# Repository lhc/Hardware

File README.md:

# Desenvolvimento de HW LHC
Desde a sua fundação vários projetos de HW Hardware abertos foram desenvolvidos no LHC, usando diferentes processadores e ferramentas. Este repositório contém todos os projetos já desenvolvidos no LHC.

# Contribua e participe dos projetos com Hardware no LHC
Acesse o nosso forms e se conecte ao time do Laboratório Hacker de Campinas, através da criação de sua conta no forum e conversando com o pessoal sobre os diversos projetos. [https://discourse.lhc.net.br](https://discourse.lhc.net.br/c/hardware/21)

# Projetos
 2024
- [LHCbit](https://github.com/lhc/Hardware/tree/main/LHCbit)
- 
- [Venda limitada, pegue a sua placa antes que acabe](https://forms.gle/h3qhtFoRbykofKP68)
- [Construindo sua placa em KICAD](https://github.com/lhc/Hardware/tree/main/Oficinas/monte-sua-placa-kicad)
- [nodeLHC](https://github.com/lhc/Hardware/tree/main/nodeLHC)
- [nodeLHC-ESP32](https://github.com/lhc/Hardware/tree/main/nodeLHC-ESP32)

# Oficinas
- [Evento: Construindo sua placa em KiCad](https://github.com/lhc/Hardware/tree/main/Oficinas/monte-sua-placa-kicad)

# Portes
- [Porte da LHCbit para NuttX](https://github.com/apache/nuttx/blob/master/Documentation/platforms/xtensa/esp32s3/boards/esp32s3-lhcbit/index.rst)

# Bibliotecas
- [KiCad LHC](https://github.com/lhc/Hardware/tree/main/Libraries/lhc_kicad_library)

# Contribuidores
- Leandro Pereira
- Douglas Esteves
- Jorge Guzman
- Manassés Souza
- Marcelo Junqueira
- Matheus Brito
- Estevan
- Pedro Minatel
- Rafael Estevam
- Alexandre Fernandes
- Rodrigo Azevedo
- Gustavo Ortenzi

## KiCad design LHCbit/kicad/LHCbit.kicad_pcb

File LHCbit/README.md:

# LHCBbit

# O que é esse repositório ou projeto?
LHCbit  é uma placa de desenvolvimento para a comunidade, uma ferramenta de aprendizado open-source, composta por:
- ESP32-S3 - Microcontrolador com wifi e bluetooth
- STM32WLE5 - Microcontrolador ARM cortex M4 com LoRa
- Display LCD color 0.96
- LED RGB
- 2 botões
- Conector USB type C
- Padrão Microbit, sendo possível usar todos os projetos open source voltadas para a microbit.

- 

Esse repositório fica com os principais arquivos do hardware LHCbit, lista BOM (bill of material)  e logs da evolução do projeto como texto sobre via readme.md, com chamadas, links, pré-vendas e atualização das etapas da execução do projeto aberto.

Como todo repositório de projeto é algo vivo e com constantes atualizações e melhorias no projeto, então fique convidado a colaborar.

# Como funciona?
É um projeto aberto e colaborativo, funciona de forma bem simples, basta entrar em contato com os participantes e comparecer nas atividades anunciadas pelo Laboratório Hacker de Campinas, esse projeto envolve pessoas que realizaram o desenvolvimento em seu tempo livre e conforme sua disponibilidade. Para mais detalhes procurar as pessoas envolvidas que um projeto inclusive e estão disponíveis para explicar e coletar feedback.

O Projeto tem sua licença descrita, basta contribuir, replicar, comentar, é interessante notificar e passar feedback do que foi feito ou melhorias para o projeto manter sua evolução de aprimoramento, também citar e manter a licença que foi dada ao projeto.

# Quem usará esse repositório ou projeto?
Hackers, desenvolvedores de hardware, professores com interesse em construções de placas PCB, Pesquisadores universitários e técnicos e entusiastas que usarão esse repositório, não temos muitas restrições. Podendo utilizar esse projeto e algumas referências de projetos anteriores para aprender, replicar, desenvolver em cima evoluindo a ideia e projeto, citar em projeto ou usar aprendizagem envolvida para construções de novos projetos. Basta manter a ética e respeitar as licenças de projetos abertos.

# Qual o objetivo deste projeto?
O objetivo deste projeto é a construção de um hardware aberto e colaborativo para que pessoas consigam desenvolver seus projetos pessoais, ou conjuntos de pessoas passe pelas etapas de desenvolvimento de hardware até uma implementação de aplicação com o hardware desenvolvido. Ganhando experiência no que tem de tecnologia disponível para hardware e suas aplicações.

Teremos novas etapas desse projeto que é execuções de atividades e projetos com esse hardware. Para isso acompanhe a nossa lista de discussão sobre:

# Como faço para que esse projeto funcione na minha máquina?
Para que você consiga ter uma boa experiência em baixar os arquivos na sua máquina, conseguindo replicar, modificar ou desenvolver. Basta baixar os arquivos em seu equipamento local, utilizar as ferramentas adequadas para edição e construções do projeto.

Os esquemáticos foram escritos com a ferramenta [Altium](https://www.altium.com/), mas contribuições para portar para outras ferramentas serão bem vindas.
A princípio pode ser utilizado [essa ferramenta web](https://www.altium.com/viewer/) para visualizar os esquemáticos.

As evoluções do firmware (getting started) poderão ser acompanhadas [nesse projeto](https://github.com/lhc/LHCbit/tree/main)

# Como posso ajudar neste projeto?
Você também pode contribuir de diversas formas, seja revisando a documentação, arquivos CAD do hardware.
Gerando um PR Pull Request de melhorias conforme suas experiências e testes sobre hardware.
Divulgar e marcar o projeto nas redes sociais ou citar os nossos links como referência, ou até mesmo escrevendo e participando dos nossos encontros.

# Qual a licença para este projeto ?
Esse projeto está sobre a licença:
[Revisando arquivo de licença]

# Fotos do projeto

# Checklist Review 0.1
- O VCC e GND estava em curto, revisado por Leandro Pereira

# Checklist Review 0.2

| Itens           | Check | Double Check  |
|---------------------|----------|----------|
| Alimentação 3V3| OK |  |
| LoRa RAK3172-SiP|  |  |
| Reset e Boot| OK |  |
| USB Type C | OK |  |
| OLED|  |  |
| ESP32-S3-16R8 pinout| OK |  |

- [x] [Bill of Materials BOM](Templates/BOM%20Default%20Template.xlsx)

Oficina de apresentação do projeto
[definindo] eventos.lhc.net.br

# Equipe
 - Leandro Pereira
 - Douglas Esteves
 - Manasses
 - Matheus Brito
 - Marcelo Junqueira
 - Estevan

# Agradecimentos especial aos apoiadores do Projeto
- Daniel Barbosa
- L.
- Juliana Karoline
- Fabio Barros
- Luciano Ramalho
- Jomar Silva
- Estevan Castilho

# LOG
- 24/07/2024 Status do projeto (e-mail aos apoiadores)
- 18/07/2024 Reunião interna para apresentar LHCbit aos associados e definiação da fabricação da pcb para o display
- 12/07/2024 Update e consulta aos apoiadores do projeto (e-maisl aos apoiadores)
- 20/06/2024 Reunião interna para comunicar apoiadores e documentar projeto
- 13/06/2024 Status do projeto (e-mail aos apoiadores)
- 25/04/2024 update README
- 15/08/2024 Montagem final da LHCbit edition collectibles
- 05/09/2024 Apresentação sobre o projeto no LHC e remoto
- 12/09/2024 [Porte da LHCbit para NuttX](https://github.com/apache/nuttx/blob/master/Documentation/platforms/xtensa/esp32s3/boards/esp32s3-lhcbit/index.rst)
- 26/09/2024 Reunião e avaliação do github
- 03/10/2024 Reunião e revisão de hardware e github

# Contatos:
 - [Discourse](https://discourse.lhc.net.br/c/hardware/21)

# Contribuidores

<table>
<tr>
    <td align="center" style="word-wrap: break-word; width: 127.5; height: 127.5">
        <a href=https://github.com/EstevesDouglas>
            
            <br />
            <sub style="font-size:14px"><b>Douglas Esteves</b></sub>
        </a>
    </td>
    <td align="center" style="word-wrap: break-word; width: 127.5; height: 127.5">
        <a href=https://github.com/LeandroTE>
            
            <br />
            <sub style="font-size:14px"><b>Leandro Pereira</b></sub>
        </a>
    </td>
    <td align="center" style="word-wrap: break-word; width: 127.5; height: 127.5">
        <a href=https://github.com/manasouza>
            
            <br />
            <sub style="font-size:14px"><b>Manassés Loiola de Souza</b></sub>
        </a>
    </td>
</tr>
</table>

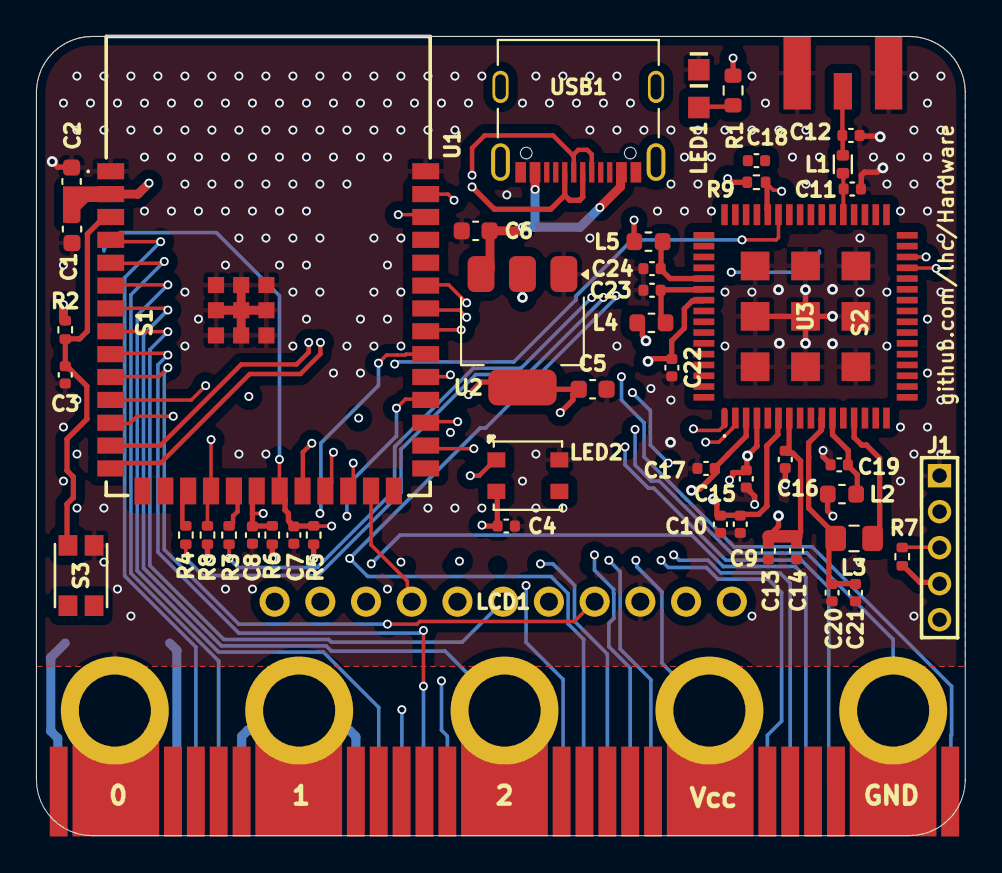
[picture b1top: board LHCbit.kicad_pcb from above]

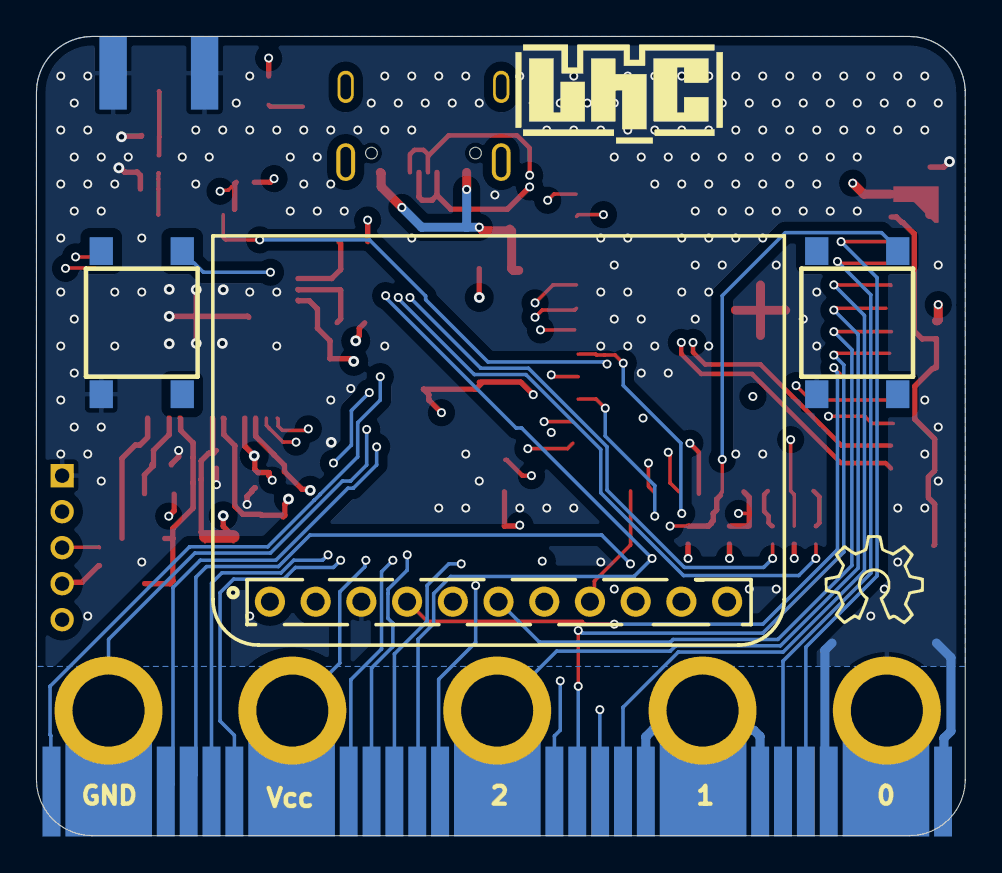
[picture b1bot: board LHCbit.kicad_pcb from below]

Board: 4 copper layers, 51.6 x 44.4 mm, 51 parts (4 on the bottom side), 46 nets.

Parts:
C1, C2, C5, C6: C-EUC0603; C_0603_1608Metric
C3, C4, C7, C8, C9, C10, C11, C12, C13, C14, C15, C16, C17, C18, C19, C20, C21, C22, C23, C24: C-EUC0402; C_0402_1005Metric
J1: 62000511121
JX1: SMACONNECTOR_EDGE_UFL; SMA_EDGELAUNCH_UFL
L1: Ferrite bead 0402; L0402 - rounded
L2, L4, L5: Ferrite bead 0603; L_0603_1608Metric
L3: L_0805_2012Metric_Pad1.15x1.40mm_HandSolder
LCD1: Adafruit 0.96" TFT LCD; ADafruit_0.96_Display
LED1: CHIPLED_0805
LED2: SK6812MINI_NOPoly; SK6812MINI
MB1: MICRO:BIT_EDGE; MICROBIT_EDGE
R1: R-US_R0603; R_0603_1608Metric
R2, R3, R4, R5, R6, R7, R8, R9: R-US_R0402; R_0402_1005Metric
S1, S2: DTSM-6; Tactile_6.6x6x4.3_DTSM-6
S3: 434153017835; 434153017835_3.2x2.9x1.7
U1: ESP32-S3-WROOM-1; ESP32S3WROOM1N16R2
U2: NCP1117LP; SOT-223
U3: RAK3172-SiP; RAK3172SiP
USB1: USB-Type-C-12402012E212A; AMPHENOL_12402012E212A

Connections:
+3V3: C1.1, C2.1, C4.2, C5.1, C9.1, C10.1, C13.1, C14.1, C15.1, C16.1, C17.1, C22.1, J1.4, L2.1, L4.1, L5.1, LCD1.1 (VIN), LED2.4 (VDD), MB1.Vcc (+3.3V), R1.2, R2.2, R5.2, R6.2, R7.2, R8.2, R9.2, U1.2 (3V3), U2.2 (VO), U2.4 (VO), U3.3 (VDD_1), U3.4 (VBAT), U3.6 (VREF+), U3.7 (VDDA), U3.55 (VDD_2)
/BOOT_STM32: R8.1, U1.18 (IO10), U3.43 (BOOT0)
/CS: MB1.P16 (#16/P0.16), U1.6 (IO6)
/D+: U1.14 (IO20), USB1.A6 (D+_A), USB1.B6 (D+_B)
/D-: U1.13 (IO19), USB1.A7 (D-_A), USB1.B7 (D-_B)
/EN: C3.1, R2.1, S3.3, U1.3 (EN)
/ESP_UART1_RX: R3.1, U1.19 (IO11)
/ESP_UART1_TX: R4.1, U1.17 (IO9)
/LED_RGB: LED2.3 (DI), U1.22 (IO14)
/LORA_RX: R4.2, U3.30 (PA3/UART2_RX)
/LORA_TX: R3.2, U3.29 (PA2/UART2_TX)
/MISO: LCD1.5 (MISO), MB1.P14 (#14/MISO/P0.22), U1.9 (IO16)
/MOSI: LCD1.6 (MOSI), MB1.P15 (#15/MOSI/P0.21), U1.8 (IO15)
/NRST: J1.5, R9.1, U1.11 (IO18), U3.44 (NRST)
/P0: MB1.P0 (PAD1/AIN2/P0.01), U1.38 (IO2)
/P1: MB1.P1 (PAD2/AIN3/P0.02), U1.31 (IO38)
/P2: MB1.P2 (PAD3/AIN4/P0.03), U1.7 (IO7)
/P3: MB1.P3 (#3/LEDCOL1/AIN5/P0.04), U1.39 (IO1)
/P4: MB1.P4 (#4/LEDCOL2/AIN6/P0.05), U1.35 (IO42)
/P6: MB1.P6 (#6/LEDCOL9/P0.12), U1.34 (IO41)
/P7: MB1.P7 (#7/LEDCOL8/P0.11), U1.33 (IO40)
/P8: MB1.P8 (#8/P0.18), U1.29 (IO36)
/P9: MB1.P9 (#9/LEDCOL7/P0.10), U1.28 (IO35)
/P10: MB1.P10 (#10/LEDCOL3/AIN7/P0.06), U1.24 (IO47)
/P12: MB1.P12 (#12/P0.20), U1.12 (IO8)
/RF_Output: C11.2, L1.1, U3.37 (RF_OUT)
/SCK: LCD1.4 (SCK), MB1.P13 (#13/SCK/P0.23), U1.10 (IO17)
/SCL: MB1.P19 (#19/SCL/P0.00), U1.5 (IO5)
/SDA: MB1.P20 (#20/SDA/P0.30), U1.4 (IO4)
/SDCS: LCD1.10 (SDCS), U1.32 (IO39)
/SW1: C7.1, MB1.P5 (#5/BUTTON_A/P0.17), R5.1, S1.4, U1.21 (IO13)
/SW2: C8.1, MB1.P11 (#11/BUTTON_B/AIN0/P0.26), R6.1, S2.4, U1.20 (IO12)
/TFTCS: LCD1.7 (TFTCS), U1.23 (IO21)
/TFTRESET: LCD1.8 (RESET), U1.25 (IO48)
/TFT_DC: LCD1.9 (TFTDC), U1.30 (IO37)
/T_SWCLK: J1.2, U3.2 (PA14)
/T_SWDIO: J1.3, R7.1, U3.1 (PA13)
GND: C1.2, C2.2, C3.2, C4.1, C5.2, C6.2, C7.2, C8.2, C9.2, C10.2, C11.1, C12.1, C13.2, C14.2, C15.2, C16.2, C17.2, C19.2, C20.2, C21.2, C22.2, C23.2, C24.2, J1.1, JX1.GND@1 (GND1), JX1.GND@2 (GND2), JX1.GND@3 (GND3), JX1.GND@4 (GND4), LCD1.3 (GND), LED1.C, LED2.2 (VSS), MB1.GND, S1.1, S2.1, S3.4, U1.1 (GND_1), U1.40 (GND_2), U1.41 (GND_3), U1.42 (GND_4), U1.43 (GND_5), U1.44 (GND_6), U1.45 (GND_7), U1.46 (GND_8), U1.47 (GND_9), U1.48 (GND_10), U1.49 (GND_11), U2.1 (GND), U3.12 (GND_1), U3.28 (GND_2), U3.35 (GND_3), U3.36 (GND_4), U3.38 (GND_5), U3.39 (GND_6), U3.46 (GND_7), U3.47 (GND_8), U3.52 (GND_9), U3.56 (GND_10), U3.65 (GND_11), U3.66 (GND_12), U3.67 (GND_13), U3.68 (GND_14), U3.69 (GND_15), U3.70 (GND_16), U3.71 (GND_17), U3.72 (GND_18), U3.73 (GND_19), USB1.A1_B12 (GND), USB1.B1_A12 (GND)
unnamed: C12.2, JX1.P (ANT), L1.2
unnamed: LED1.A, R1.1
unnamed: C19.1, L2.2, U3.11 (VDDMPS)
unnamed: C24.1, L5.2, U3.53 (VDDPA)
unnamed: C23.1, L4.2, U3.54 (VDDRF)
unnamed: C20.1, C21.1, L3.1, U3.10 (VFBSMPS)
unnamed: L3.2, U3.13 (VLXSMPS)
Vbus: C6.1, U2.3 (V+), USB1.A4_B9 (VBUS), USB1.B4_A9 (VBUS)

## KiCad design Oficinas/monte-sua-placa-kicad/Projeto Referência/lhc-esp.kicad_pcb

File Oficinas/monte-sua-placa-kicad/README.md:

# Evento: Construindo sua placa em KICAD

Repositório do evento "Construindo sua placa em KICAD"

Página do Evento: https://eventos.lhc.net.br/event/live-construindo-sua-placa-em-kicad

Link da Live: https://www.youtube.com/watch?v=B9zf6GB_SSQ

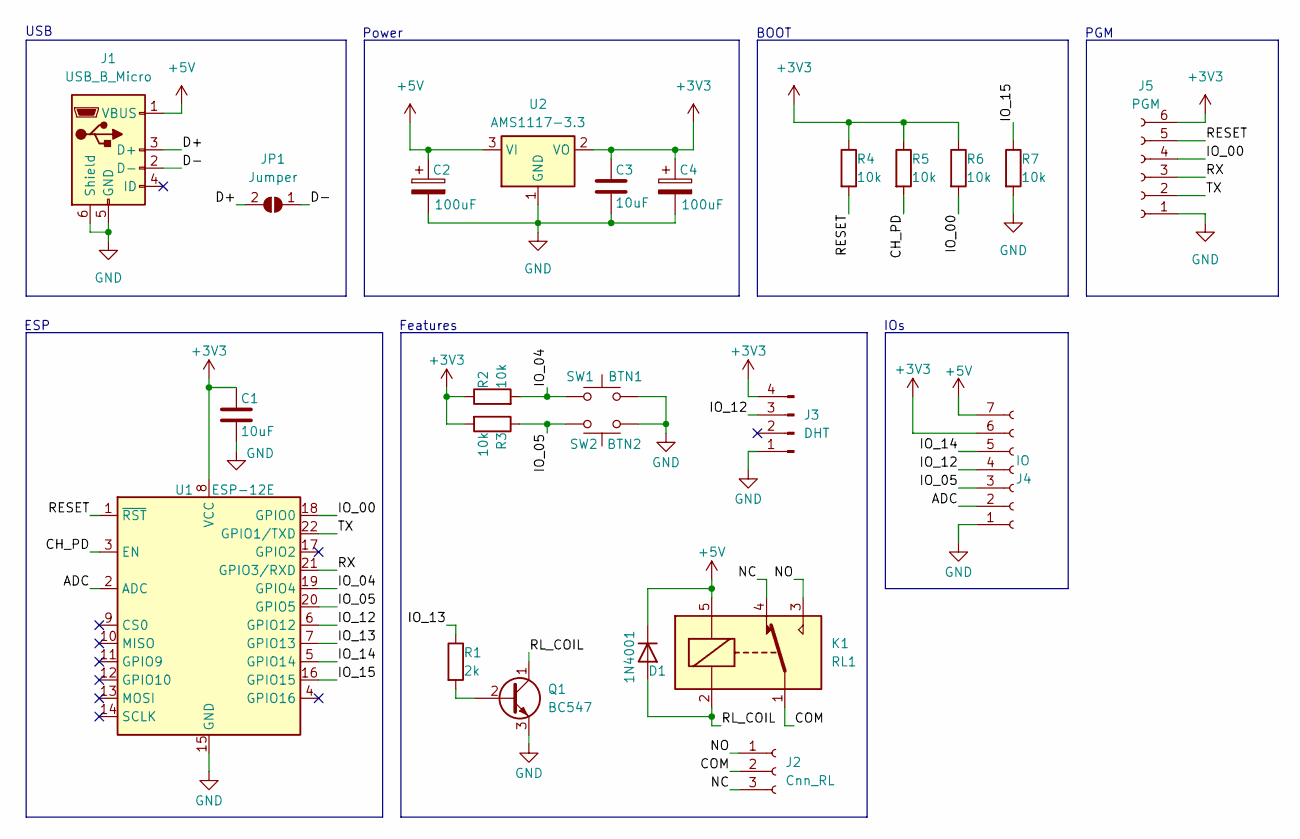
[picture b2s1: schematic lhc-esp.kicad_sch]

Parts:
C1, C3: 10uF; C_0805_2012Metric_Pad1.18x1.45mm_HandSolder
C2, C4: 100uF; CP_Radial_D5.0mm_P2.50mm
D1: 1N4001; D_SMA_Handsoldering
J1: USB_B_Micro; USB_Micro-B_GCT_USB3076-30-A
J2: Cnn_RL; TerminalBlock_bornier-3_P5.08mm
J3: DHT; PinHeader_1x04_P2.54mm_Vertical
J4: IO; PinHeader_1x07_P2.54mm_Vertical
J5: PGM; PinHeader_1x06_P2.54mm_Vertical
JP1: Jumper; SolderJumper-2_P1.3mm_Open_RoundedPad1.0x1.5mm
K1: RL1; Relay_SPDT_SANYOU_SRD_Series_Form_C
Q1: BC547; TO-92_Inline
R1: 2k; R_0805_2012Metric_Pad1.20x1.40mm_HandSolder
R2, R3, R4, R5, R6, R7: 10k; R_0805_2012Metric_Pad1.20x1.40mm_HandSolder
SW1: BTN1; SW_PUSH_6mm
SW2: BTN2; SW_PUSH_6mm
U1: ESP-12E
U2: AMS1117-3.3; SOT-223-3_TabPin2

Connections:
+3V3: C1.1, C3.1, C4.1, J3.4, J4.6, J5.6, R2.1, R3.2, R4.1, R5.1, R6.1, U1.8 (VCC), U2.2 (VO)
+5V: C2.1, D1.1 (K), J1.1 (VBUS), J4.7, K1.5, U2.3 (VI)
/ADC: J4.2, U1.2 (ADC)
/CH_PD: R5.2, U1.3 (EN)
/COM: J2.2, K1.1
/D+: J1.3 (D+), JP1.2 (B)
/D-: J1.2 (D-), JP1.1 (A)
/IO_00: J5.4, R6.2, U1.18 (GPIO0)
/IO_04: R2.2, SW1.1, U1.19 (GPIO4)
/IO_05: J4.3, R3.1, SW2.2, U1.20 (GPIO5)
/IO_12: J3.3, J4.4, U1.6 (GPIO12)
/IO_13: R1.1, U1.7 (GPIO13)
/IO_14: J4.5, U1.5 (GPIO14)
/IO_15: R7.1, U1.16 (GPIO15)
/NC: J2.3, K1.4
/NO: J2.1, K1.3
/RESET: J5.5, R4.2, U1.1 (~RST)
/RL_COIL: D1.2 (A), K1.2, Q1.1 (C)
/RX: J5.3, U1.21 (GPIO3/RXD)
/TX: J5.2, U1.22 (GPIO1/TXD)
GND: C1.2, C2.2, C3.2, C4.2, J1.5 (GND), J1.6 (Shield), J3.1, J4.1, J5.1, Q1.3 (E), R7.2, SW1.2, SW2.1, U1.15 (GND), U2.1 (GND)
unnamed: Q1.2 (B), R1.2

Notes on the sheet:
USB
BOOT
IOs
PGM
Power
Features
ESP

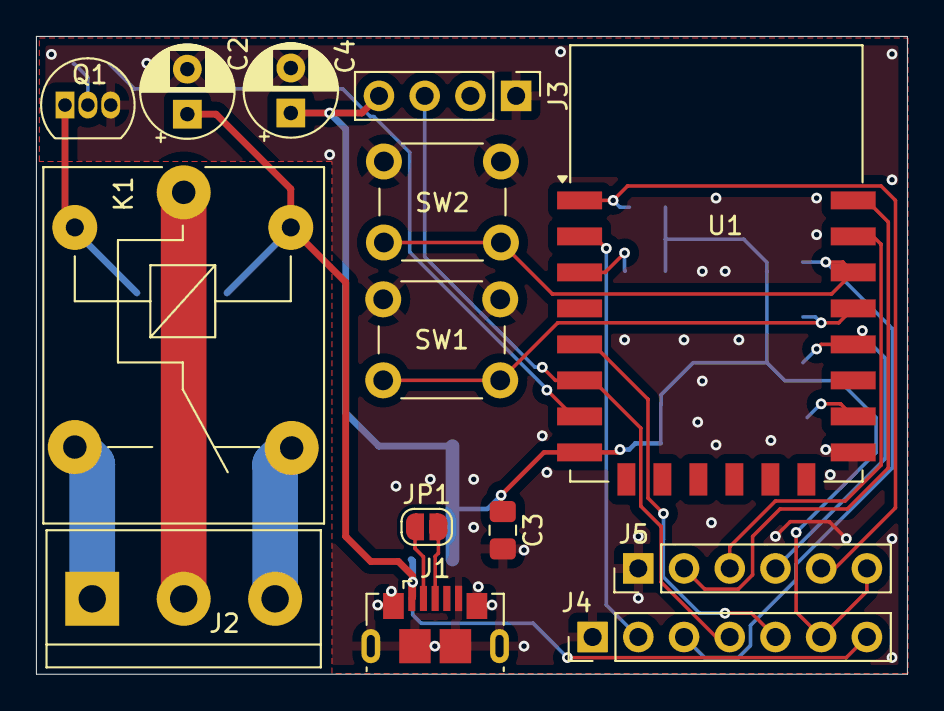
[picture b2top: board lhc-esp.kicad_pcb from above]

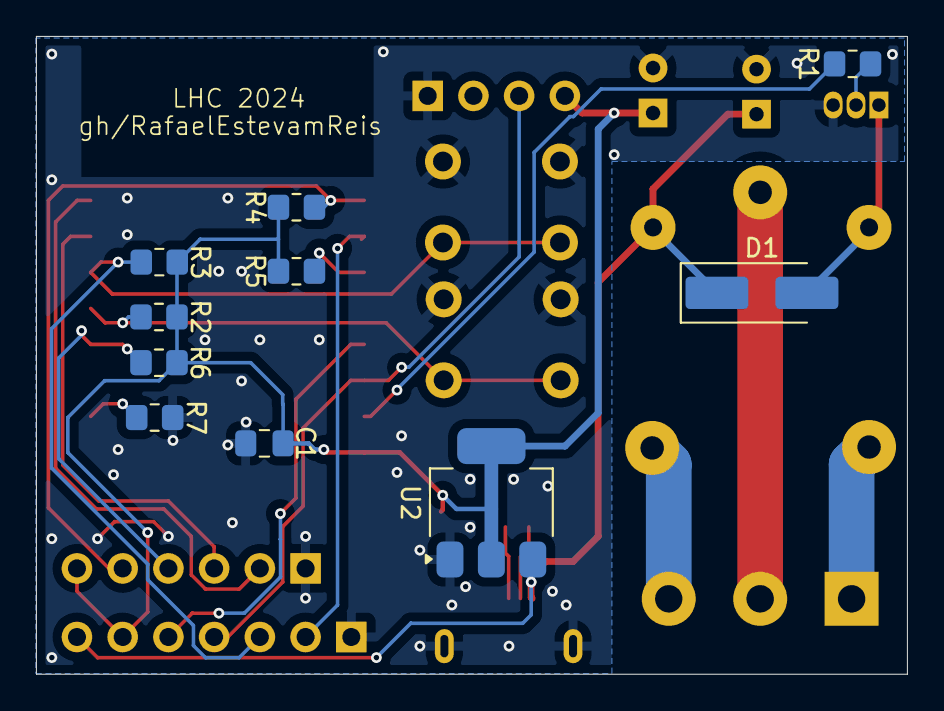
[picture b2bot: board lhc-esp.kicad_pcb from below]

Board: 2 copper layers, 48.4 x 35.4 mm, 24 parts (10 on the bottom side), 22 nets.

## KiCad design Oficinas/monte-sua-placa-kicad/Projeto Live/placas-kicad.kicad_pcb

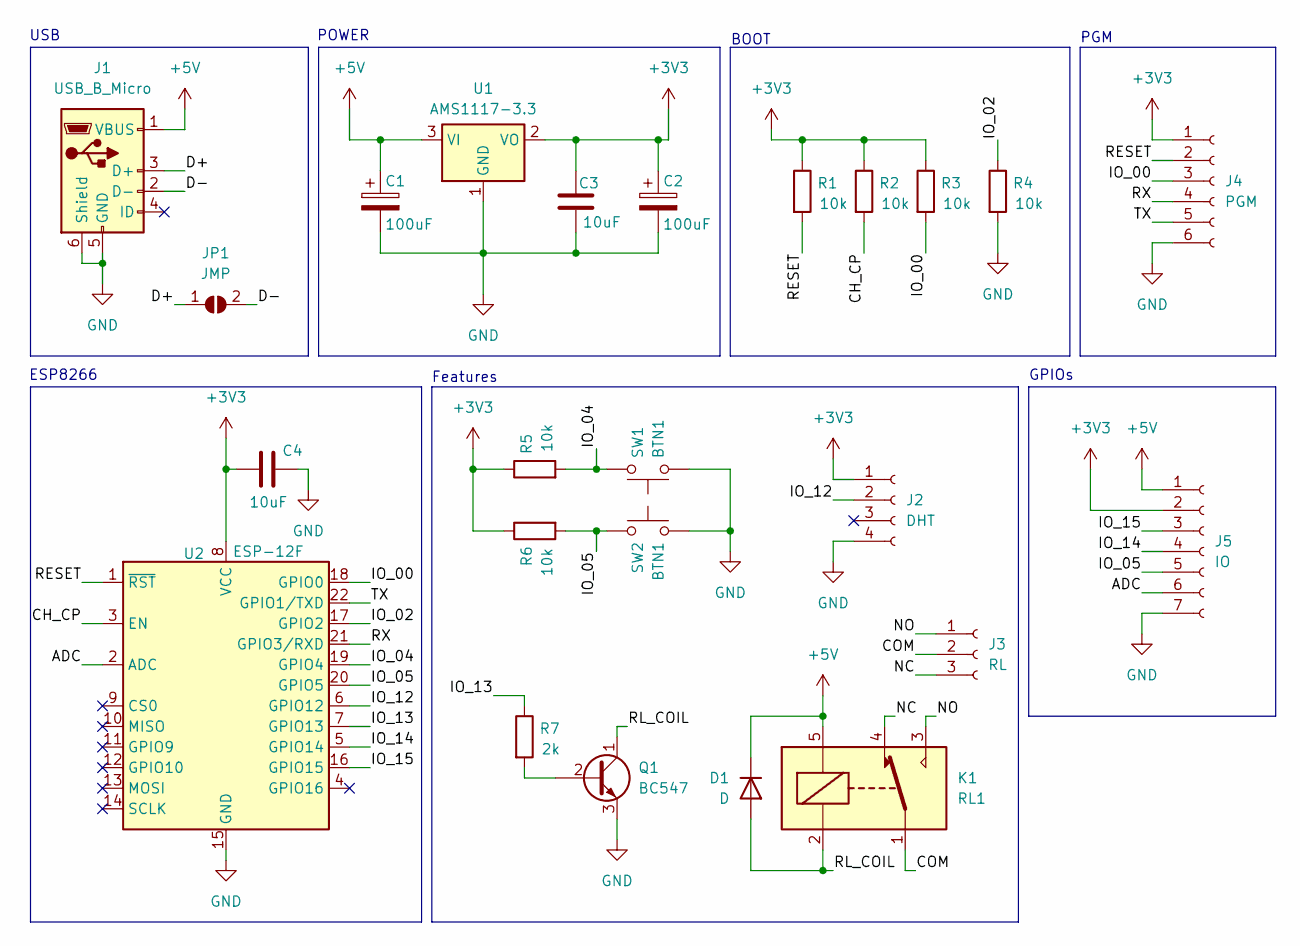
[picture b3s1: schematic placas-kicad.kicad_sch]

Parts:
C1, C2: 100uF; CP_Radial_D5.0mm_P2.50mm
C3, C4: 10uF; C_0805_2012Metric_Pad1.18x1.45mm_HandSolder
D1: D; D_SMA-SMB_Universal_Handsoldering
J1: USB_B_Micro; USB_Micro-B_GCT_USB3076-30-A
J2: DHT; PinSocket_1x04_P2.54mm_Vertical
J3: RL; TerminalBlock_bornier-3_P5.08mm
J4: PGM; PinHeader_1x06_P2.54mm_Vertical
J5: IO; PinHeader_1x07_P2.54mm_Vertical
JP1: JMP; SolderJumper-2_P1.3mm_Open_RoundedPad1.0x1.5mm
K1: RL1; Relay_SPDT_SANYOU_SRD_Series_Form_C
Q1: BC547; TO-92_Inline
R1, R2, R3, R4, R5, R6: 10k; R_0805_2012Metric_Pad1.20x1.40mm_HandSolder
R7: 2k; R_0805_2012Metric_Pad1.20x1.40mm_HandSolder
SW1, SW2: BTN1; SW_PUSH_6mm
U1: AMS1117-3.3; SOT-223-3_TabPin2
U2: ESP-12F; ESP-12E

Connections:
+3V3: C2.1, C3.1, C4.2, J2.1, J4.1, J5.2, R1.1, R2.1, R3.1, R5.1, R6.1, U1.2 (VO), U2.8 (VCC)
+5V: C1.1, D1.1 (K), J1.1 (VBUS), J5.1, K1.5, U1.3 (VI)
/ADC: J5.6, U2.2 (ADC)
/CH_CP: R2.2, U2.3 (EN)
/COM: J3.2, K1.1
/D+: J1.3 (D+), JP1.1 (A)
/D-: J1.2 (D-), JP1.2 (B)
/IO_00: J4.3, R3.2, U2.18 (GPIO0)
/IO_02: R4.1, U2.17 (GPIO2)
/IO_04: R5.2, SW1.2, U2.19 (GPIO4)
/IO_05: J5.5, R6.2, SW2.2, U2.20 (GPIO5)
/IO_12: J2.2, U2.6 (GPIO12)
/IO_13: R7.1, U2.7 (GPIO13)
/IO_14: J5.4, U2.5 (GPIO14)
/IO_15: J5.3, U2.16 (GPIO15)
/NC: J3.3, K1.4
/NO: J3.1, K1.3
/RESET: J4.2, R1.2, U2.1 (~RST)
/RL_COIL: D1.2 (A), K1.2, Q1.1 (C)
/RX: J4.4, U2.21 (GPIO3/RXD)
/TX: J4.5, U2.22 (GPIO1/TXD)
GND: C1.2, C2.2, C3.2, C4.1, J1.5 (GND), J1.6 (Shield), J2.4, J4.6, J5.7, Q1.3 (E), R4.2, SW1.1, SW2.1, U1.1 (GND), U2.15 (GND)
unnamed: Q1.2 (B), R7.2

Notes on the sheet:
BOOT
POWER
PGM
Features
ESP8266
GPIOs
USB

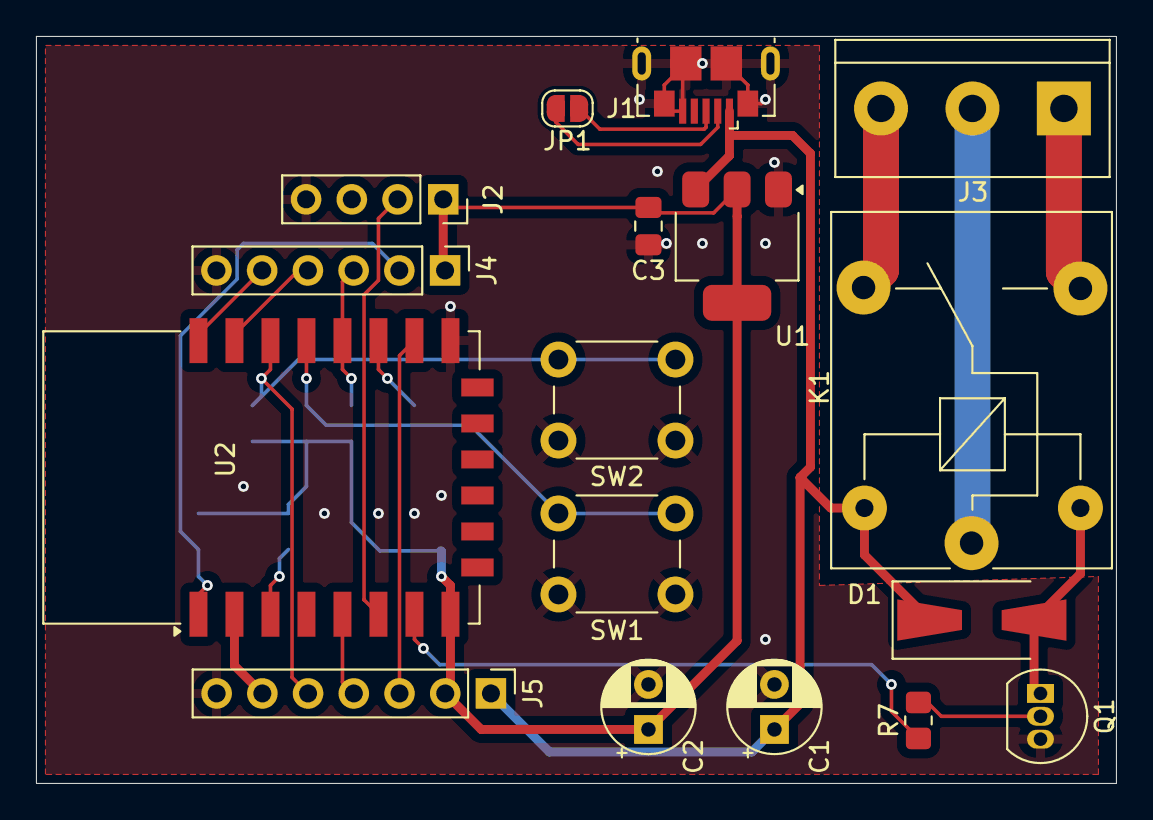
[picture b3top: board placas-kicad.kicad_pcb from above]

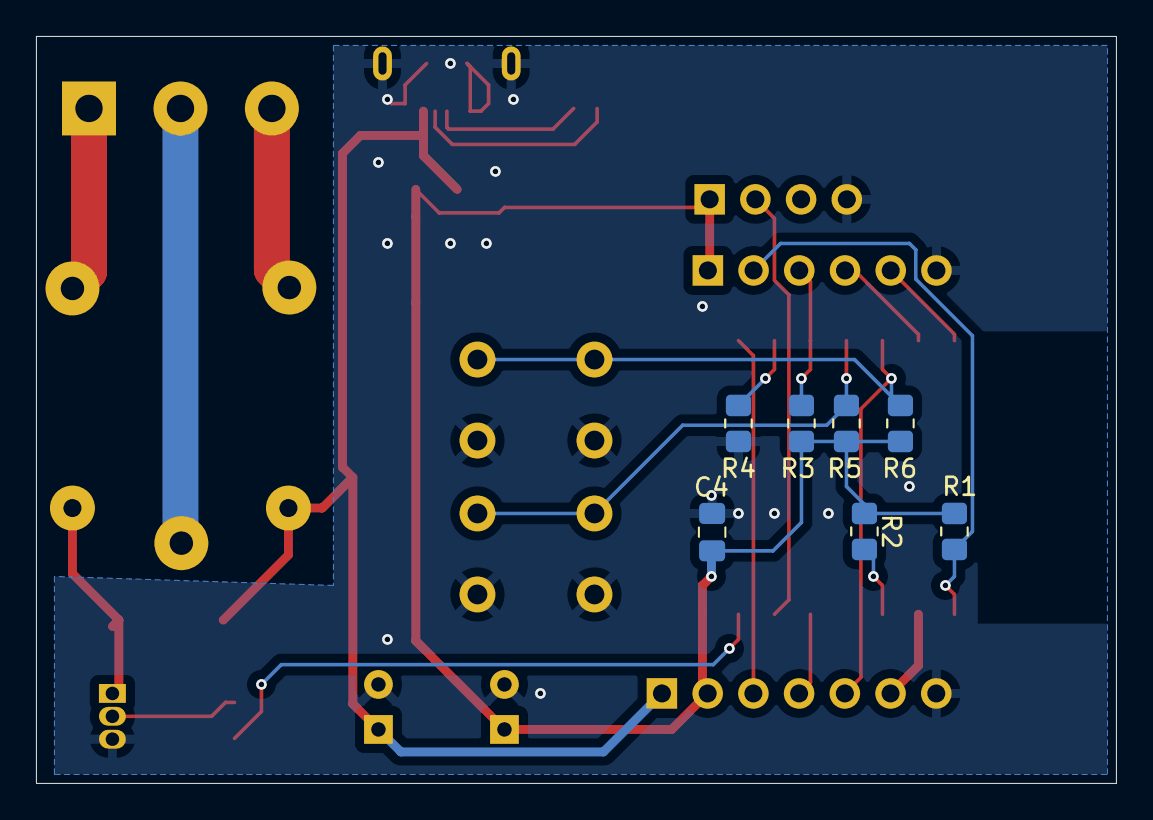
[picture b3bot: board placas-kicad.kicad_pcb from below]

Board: 2 copper layers, 60.0 x 41.5 mm, 24 parts (7 on the bottom side), 23 nets.

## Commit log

2023-12-16 Commit inicial
2023-12-17 Mudança para o rak-3172-sip
2023-12-22 Adicionado todos os componentes
2024-02-28 Conclusão do esquemático
2024-02-28 Update do arquivo pcb
2024-02-29 Conclusão do posicionamento dos componentes
2024-04-12 Conclusão do projeto com redução do tamanho do plano de ground
2024-04-15 Correção curto do footprint do conector microbit
2024-04-15 Atualização de BOM com componentes 0402
2024-04-18 Inclusão da BOM
2024-04-19 Ajuste BOM para fabricação
2024-04-19 Ajuste draftsman
2024-04-29 Junção de todos os projetos de HW
2024-05-01 Update README: removendo duplicações e organizando links
2024-06-20 Updated docs LHCbit
2024-07-18 Update README.md: nomes apoiadores
2024-07-19 update README: seção ambiente local
2024-07-19 Update README.md Correção gramatical texto em Pt-br
2024-07-27 add auto-add contributors action
2024-07-27 Update README.md: contributors reference
2024-07-28 docs(README): update contributors
2024-07-28 Update README.md: seção contributors
2024-08-17 separando arquivos altium
2024-08-22 teste da importação dos arquivos altium
2024-08-24 update gitignore
2024-08-27 update README: contributors
2024-08-28 docs(README): update LHCBit contributors
2024-08-30 Fixed display footprint
2024-08-30 Fixed LHCbit display
2024-08-30 Added keepout for usb connector
2024-09-05 Fixed display pinout
    Version 2.0 LHCbit
2024-09-13 Added reset button for LHCbit
2024-10-04 Improved silkscreen of LHCbit
2024-10-09 Versão preliminar da placa LHCbit importada para o Kicad, ainda faltam pequenos ajustes de posicionamento, camadas e correção dos erros de DRC.
2024-10-31 Changed button s2 to IO0 and added header for uart
